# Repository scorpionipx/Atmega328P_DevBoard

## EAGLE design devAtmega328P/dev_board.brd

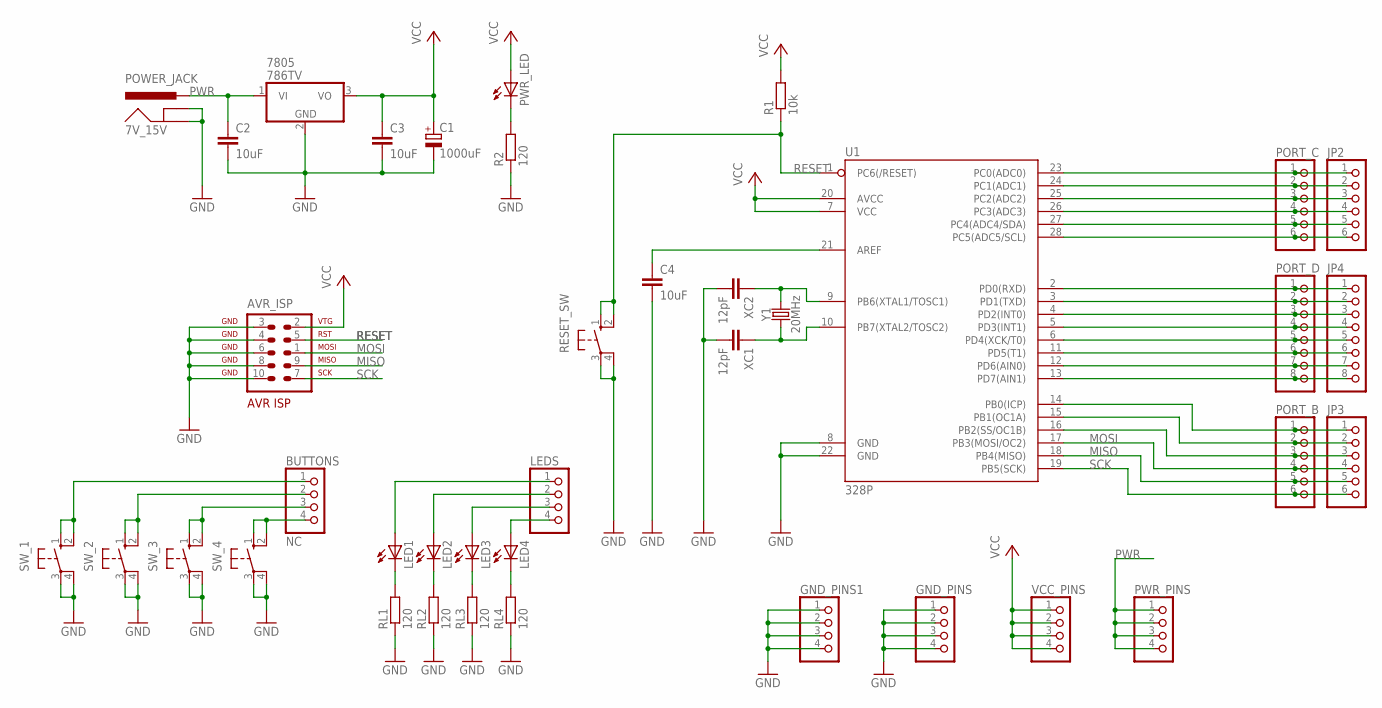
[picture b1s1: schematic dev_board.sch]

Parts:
7V_15V: POWER_JACK; POWER_JACK_PTH
7805: 786TV; TO220V
AVR_ISP: AVR-ISP-10
BUTTONS: NC; 1X04
C1: 1000uF; E3,5-10
C2, C3, C4: 10uF; C025-025X050
GND_PINS, GND_PINS1: PINHD-1X4; 1X04
JP2, JP3: PINHD-1X6; 1X06
JP4: PINHD-1X8; 1X08
LED1, LED2, LED3, LED4: LED5MM
LEDS: PINHD-1X4; 1X04
PORT_B: PINHD-1X6; 1X06
PORT_C: PINHD-1X6; 1X06
PORT_D: PINHD-1X8; 1X08
PWR_LED: LED3MM
PWR_PINS: PINHD-1X4; 1X04
R1: 10k; 0207/10
R2: 120; 0207/10
RESET_SW: 10-XX; B3F-10XX
RL1, RL2, RL3, RL4: 120; 0207/10
SW_1, SW_2, SW_3, SW_4: 10-XX; B3F-10XX
U1: 328P; DIP28
VCC_PINS: PINHD-1X4; 1X04
XC1, XC2: 12pF; C025-025X050
Y1: 20MHz; HC49US

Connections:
GND: 7V_15V.GND, 7V_15V.GNDBREAK, 7805.2 (GND), AVR_ISP.3, AVR_ISP.4, AVR_ISP.6, AVR_ISP.8, AVR_ISP.10, C1.-, C2.2, C3.2, C4.2, GND_PINS.1, GND_PINS.2, GND_PINS.3, GND_PINS.4, GND_PINS1.1, GND_PINS1.2, GND_PINS1.3, GND_PINS1.4, R2.1, RESET_SW.3, RESET_SW.4 (P1), RL1.1, RL2.1, RL3.1, RL4.1, SW_1.3, SW_1.4 (P1), SW_2.3, SW_2.4 (P1), SW_3.3, SW_3.4 (P1), SW_4.3, SW_4.4 (P1), U1.8 (GND), U1.22 (GND), XC1.2, XC2.2
MISO: AVR_ISP.9, JP3.5, PORT_B.5, U1.18 (PB4(MISO))
MOSI: AVR_ISP.1, JP3.4, PORT_B.4, U1.17 (PB3(MOSI/OC2))
unnamed: C4.1, U1.21 (AREF)
unnamed: JP4.1, PORT_D.1, U1.2 (PD0(RXD))
unnamed: JP4.2, PORT_D.2, U1.3 (PD1(TXD))
unnamed: PWR_LED.K (C), R2.2
unnamed: JP4.3, PORT_D.3, U1.4 (PD2(INT0))
unnamed: U1.9 (PB6(XTAL1/TOSC1)), XC2.1, Y1.2
unnamed: U1.10 (PB7(XTAL2/TOSC2)), XC1.1, Y1.1
unnamed: JP4.4, PORT_D.4, U1.5 (PD3(INT1))
unnamed: JP4.5, PORT_D.5, U1.6 (PD4(XCK/T0))
unnamed: JP4.6, PORT_D.6, U1.11 (PD5(T1))
unnamed: JP4.7, PORT_D.7, U1.12 (PD6(AIN0))
unnamed: JP4.8, PORT_D.8, U1.13 (PD7(AIN1))
unnamed: JP2.6, PORT_C.6, U1.28 (PC5(ADC5/SCL))
unnamed: JP2.5, PORT_C.5, U1.27 (PC4(ADC4/SDA))
unnamed: JP2.4, PORT_C.4, U1.26 (PC3(ADC3))
unnamed: JP2.3, PORT_C.3, U1.25 (PC2(ADC2))
unnamed: JP2.2, PORT_C.2, U1.24 (PC1(ADC1))
unnamed: JP2.1, PORT_C.1, U1.23 (PC0(ADC0))
unnamed: JP3.1, PORT_B.1, U1.14 (PB0(ICP))
unnamed: JP3.2, PORT_B.2, U1.15 (PB1(OC1A))
unnamed: JP3.3, PORT_B.3, U1.16 (PB2(SS/OC1B))
unnamed: LED4.K (C), RL4.2
unnamed: LED3.K (C), RL3.2
unnamed: LED2.K (C), RL2.2
unnamed: LED1.K (C), RL1.2
unnamed: LED4.A, LEDS.4
unnamed: LED3.A, LEDS.3
unnamed: LED2.A, LEDS.2
unnamed: LED1.A, LEDS.1
unnamed: BUTTONS.4, SW_4.1 (S), SW_4.2 (S1)
unnamed: BUTTONS.3, SW_3.1 (S), SW_3.2 (S1)
unnamed: BUTTONS.2, SW_2.1 (S), SW_2.2 (S1)
unnamed: BUTTONS.1, SW_1.1 (S), SW_1.2 (S1)
PWR: 7V_15V.PWR, 7805.1 (VI), C2.1, PWR_PINS.1, PWR_PINS.2, PWR_PINS.3, PWR_PINS.4
RESET: AVR_ISP.5, R1.1, RESET_SW.1 (S), RESET_SW.2 (S1), U1.1 (PC6(/RESET))
SCK: AVR_ISP.7, JP3.6, PORT_B.6, U1.19 (PB5(SCK))
VCC: 7805.3 (VO), AVR_ISP.2, C1.+, C3.1, PWR_LED.A, R1.2, U1.7 (VCC), U1.20 (AVCC), VCC_PINS.1, VCC_PINS.2, VCC_PINS.3, VCC_PINS.4

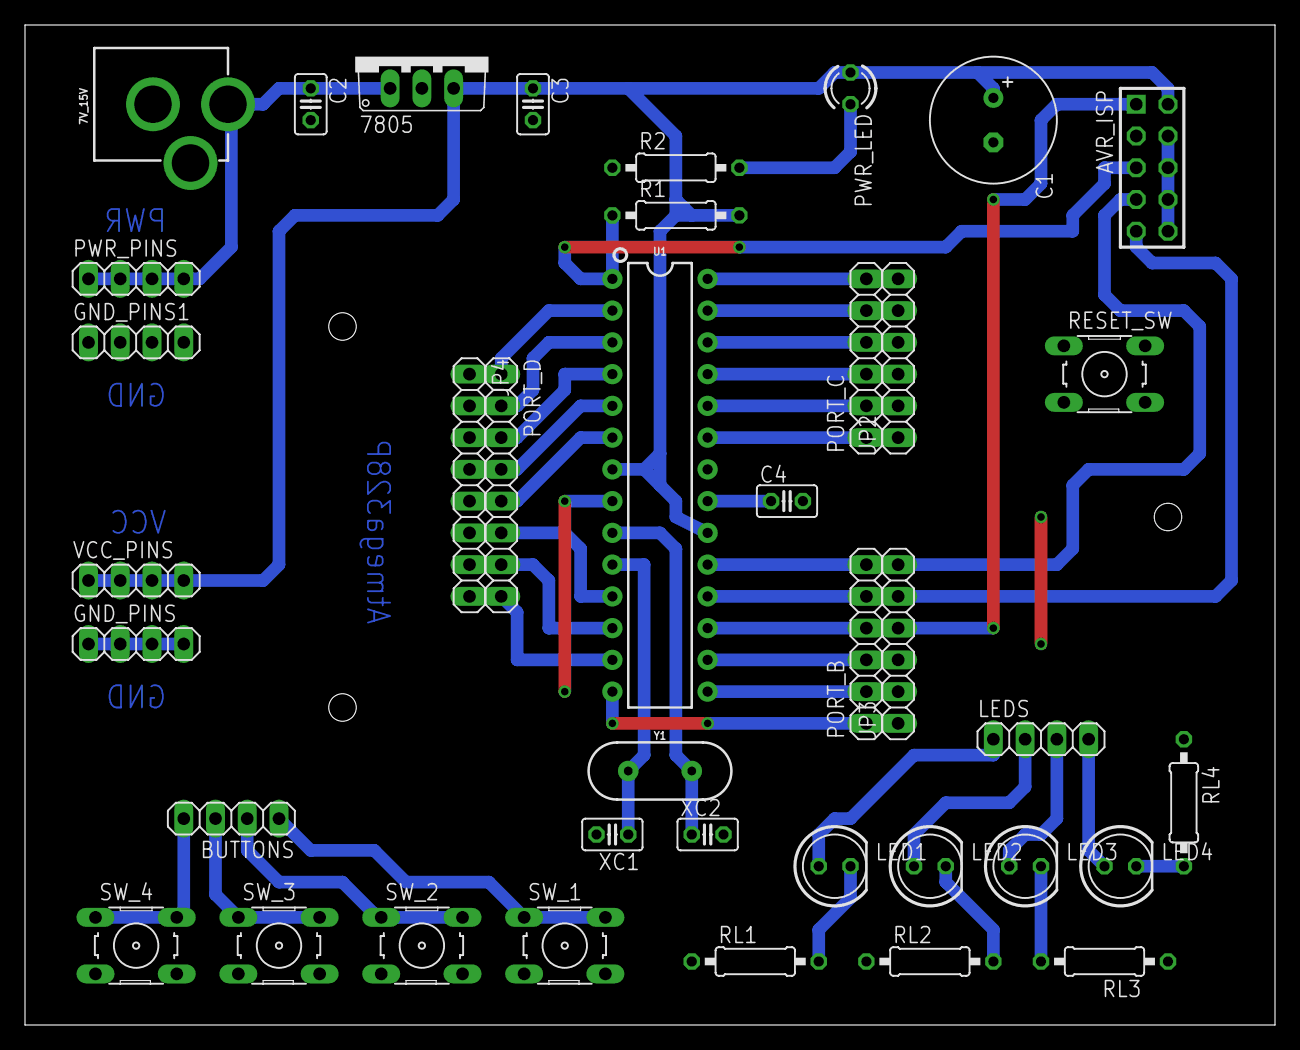
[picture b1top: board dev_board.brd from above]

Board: 2 copper layers, 100.0 x 80.0 mm, 39 parts (0 on the bottom side), 40 nets.

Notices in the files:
parts and their libraries:
SparkFun-Connectors: Licensing: Creative Commons ShareAlike 4.0 International - https://creativecommons.org/licenses/by-sa/4.0
